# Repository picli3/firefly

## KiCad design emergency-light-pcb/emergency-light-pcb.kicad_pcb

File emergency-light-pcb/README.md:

# FIREFLY — PCB de lámpara de emergencia

> Primer borrador de documentación de la placa. Las imágenes se generan directamente desde el archivo KiCad actual.

## Vista 3D

| Vista isométrica |
|---|
|  |

| Vista superior | Vista inferior |
|---|---|
|  |  |

La vista 3D no muestra el cuerpo del módulo U1 porque el modelo STEP configurado para el footprint no está disponible en la ruta local de KiCad. Sí se muestran sus pads, serigrafía y keepout.

## 1. Descripción

Esta PCB implementa el controlador y monitor de una lámpara de emergencia conectada por Zigbee. La placa integra:

- Un módulo inalámbrico **ESP32-H2-MINI-1** como controlador principal.
- Medición de corriente, tensión y potencia mediante **INA226**.
- Entrada de temperatura mediante un divisor con NTC.
- Simulación de pérdida de alimentación de la lámpara mediante un relé.
- Regulación local de `+7.5V` a `+5V` y `+3V3`.
- Conectores de prueba, NTC, sensado de corriente, alimentación y servicio USB.

El contacto del relé conmuta la señal de control `+7.5V` de la lámpara. Esta PCB no debe interpretarse como una etapa para conmutar directamente red de `220 VAC`.

## 2. Datos principales

| Parámetro | Valor |
|---|---|
| Nombre del diseño | FIREFLY |
| Revisión indicada en el proyecto | `v1.0.0` |
| Contorno de la PCB | `37 mm × 40 mm` |
| Capas de cobre utilizadas | `F.Cu` y `B.Cu` |
| Alimentación externa | `+7.5V` y `GND` mediante J4 |
| Comunicación inalámbrica | Zigbee / IEEE 802.15.4 mediante ESP32-H2 |
| Monitor de corriente | INA226, dirección I²C `0x40` |
| Shunt de corriente | R5 = `2 mΩ` |
| Relé | Songle `SRD-05VDC-SL-C`, bobina de `5V` |

## 3. Arquitectura eléctrica

```text
                           ┌───────────────┐
J4.1  +7.5V ───────────────┤ U3            ├── +3V3 ── U1 / U2 / U5
                           │ NCP1117-3.3  │
                           └───────────────┘
                                   │
                                   └───────────────┐
                                                   ▼
                           ┌───────────────┐    +5V ── K1 bobina
J4.1  +7.5V ───────────────┤ U4            ├─────────── D1 protección flyback
                           │ TPS76950     │
                           └───────────────┘

J4.2 señal AC ── R9/R10 ── U5 ── AC_STATUS ── U1 GPIO10

J3 VIN_P ── R5 2 mΩ ── VIN_N ── J3
              │       │
              └── U2 INA226 ── I²C ── U1 GPIO4/GPIO12

J2 NTC ── NTC_IN ── U1 GPIO1 / ADC1_CH0

U1 GPIO2 / EN_R ── R4 ── Q1 ── K1 bobina
                         │
                        R14
                         │
                        GND
```

### Dominios de alimentación

- `+7.5V`: entrada de la placa, alimentación de U3/U4 y señal que se entrega al controlador de la lámpara a través del contacto del relé.
- `+5V`: salida de U4 para la bobina de K1 y el circuito de protección asociado.
- `+3V3`: salida de U3 para U1, U2, U5, pull-ups y circuitos de señal.
- `GND`: retorno común de la lógica y de las fuentes de la placa.

## 4. Pinout del ESP32-H2-MINI-1

| Pin físico U1 | Señal en PCB | Función |
|---:|---|---|
| 3 | `+3V3` | Alimentación principal del módulo |
| 5 | `/EN_R` | Control del relé desde GPIO2 |
| 8 | `/EN_MCU` | Habilitación/reset del módulo |
| 10 | `/NTC_IN` | Medición del NTC, GPIO1 / ADC1_CH0 |
| 15 | `VBAT` | Nodo de alimentación interno del módulo; en la configuración por defecto no requiere alimentación externa |
| 16 | `/SCL` | I²C SCL, GPIO12 |
| 18 | `/SDA` | I²C SDA, GPIO4 |
| 19 | `/TEST_BUTTON` | Pulsador de prueba, GPIO5 |
| 20 | `/AC_STATUS` | Estado de presencia de AC, GPIO10 |
| 21 | `/ALERT` | Alerta del INA226, GPIO11 |
| 26 | `USB_D-` | USB D− mediante R13 de 22 Ω |
| 27 | `USB_D+` | USB D+ mediante R12 de 22 Ω |
| 1, 2, 11, 14, 36–53 | `GND` | Retorno y pad expuesto del módulo |

El firmware de `h2-emergency-light` utiliza el mismo contrato: SDA=`GPIO4`, SCL=`GPIO12`, relé=`GPIO2`, NTC=`GPIO1`, botón=`GPIO5`, `AC_STATUS`=`GPIO10` y `ALERT`=`GPIO11`.

El archivo del proyecto conserva el identificador de footprint `RF_Module:ESP32-C6-MINI-1`, aunque el símbolo, el valor y la asignación de pads corresponden al ESP32-H2-MINI-1. La equivalencia mecánica de la huella debe mantenerse documentada y verificada para el componente montado.

## 5. Función de los conectores

### J1 — TEST

| Pin | Señal | Función |
|---:|---|---|
| 1 | `/TEST_BUTTON` | Entrada del pulsador de prueba hacia U1 GPIO5 |
| 2 | `GND` | Retorno común |

### J2 — NTC

| Pin | Señal | Función |
|---:|---|---|
| 1 | `/NTC_IN` | Nodo del divisor NTC hacia U1 GPIO1 / ADC1_CH0 |
| 2 | `GND` | Retorno del sensor |

### J3 — Sensado de corriente

J3 expone los dos lados del shunt R5 para insertar el circuito de corriente de la lámpara y permitir que U2 mida la caída diferencial.

| Pin | Señal | Función |
|---:|---|---|
| 1 | `VIN_P` | Lado positivo del shunt, hacia INA226 VIN+ |
| 2 | `VIN_N` | Lado negativo del shunt, hacia INA226 VIN− y VBUS |

La polaridad y el sentido de corriente deben respetarse para que el signo de la medición sea el esperado por el firmware.

### J4 — POWER / señal de lámpara

| Pin | Señal | Función |
|---:|---|---|
| 1 | `+7.5V` | Entrada de alimentación de la placa y referencia para la señal de AC |
| 2 | `Net-(J4-Pin_2)` | Señal conmutada hacia el controlador de la lámpara; también alimenta el divisor R9/R10 para generar `AC_STATUS` |
| 3 | `GND` | Retorno de alimentación |

J4.2 es una señal DC de baja tensión. No debe conectarse directamente a la red eléctrica.

### J5 — USB / servicio

J5 es un header de servicio para programación o pruebas del módulo.

| Pin | Señal | Función |
|---:|---|---|
| 1 | `+7.5V` mediante R11 de 0 Ω | Alimentación expuesta del circuito de servicio |
| 2 | `USB_D-` mediante R13 de 22 Ω | USB D− hacia U1 GPIO26 |
| 3 | `USB_D+` mediante R12 de 22 Ω | USB D+ hacia U1 GPIO27 |
| 4 | `GND` | Retorno común |

El footprint de J5 está excluido actualmente de la BOM y todavía utiliza un conector genérico. Si se montará físicamente, debe definirse su número de parte y confirmar la orientación del cableado antes de fabricar.

## 6. Bloques funcionales

### U1 — ESP32-H2-MINI-1

Controlador Zigbee de la lámpara. Gestiona el relé, el botón de prueba, la temperatura, el estado de alimentación y las mediciones del INA226.

`VBAT` corresponde al nodo de alimentación interno del módulo. Según la configuración por defecto del ESP32-H2-MINI-1, está conectado internamente a la alimentación de 3,3 V; no se debe añadir una fuente externa independiente a ese pin.

### U2 — INA226AIDGSR

Monitor de corriente y potencia por I²C. Usa dirección `0x40`, pull-ups en SDA/SCL y una resistencia shunt R5 de `2 mΩ`. La alerta se entrega a U1 mediante `/ALERT`.

### U3 — NCP1117ST33T3G

Regulador lineal de `+7.5V` a `+3V3`. C3 y C4 proporcionan el filtrado de entrada y salida.

### U4 — TPS76950DBVR

Regulador lineal de `+7.5V` a `+5V`. Su salida alimenta la bobina de K1 y el circuito de rueda libre.

### U5 — NC7SZ125M5X

Buffer lógico alimentado a `+3V3`. Convierte el nivel del divisor R9/R10 en una señal limpia de `3.3V` para `AC_STATUS`/GPIO10. OE está fijado a GND para mantenerlo habilitado.

### K1, Q1 y D1 — simulación de pérdida de AC

K1 es un relé SPDT Songle `SRD-05VDC-SL-C`. Q1, controlado por U1 GPIO2 mediante R4, conmuta la bobina; R14 mantiene la compuerta en estado apagado durante reset y D1 absorbe el pulso inductivo.

La intención funcional es que el contacto normalmente cerrado mantenga presente `+7.5V` en J4.2 cuando el relé está desenergizado. Al energizar K1, el contacto se abre y la lámpara interpreta una pérdida de alimentación.

**Nota de montaje:** confirmar la correspondencia entre la numeración física del Songle y el footprint antes de liberar Gerbers. El número de pin del símbolo genérico de KiCad no sustituye la verificación contra el dibujo del fabricante.

## 7. Componentes de soporte relevantes

| Referencia | Valor | Función |
|---|---:|---|
| C1, C6, C7 | 100 nF | Desacoplo local de U2, U1 y U5 |
| C2–C5, C8 | 10 µF | Filtrado y reserva en los reguladores y U1 |
| C9 | 1 µF | Retardo RC de `/EN_MCU` junto con R1 de 10 kΩ |
| R1–R3, R6–R8, R10 | 10 kΩ | Pull-ups y polarización de señales |
| R4 | 3.3 kΩ | Resistencia serie de compuerta de Q1 |
| R5 | 2 mΩ | Shunt de medición de corriente |
| R9 | 12.4 kΩ | Rama superior del divisor de `AC_STATUS` |
| R11 | 0 Ω | Enlace de alimentación hacia J5; selección actual del proyecto |
| R12, R13 | 22 Ω | Terminación serie de USB D+/D− |
| R14 | 100 kΩ | Pull-down de compuerta de Q1 |

## 8. Estado del borrador

La documentación corresponde al estado actual de los archivos KiCad y no sustituye una liberación de fabricación. Antes de fabricar conviene completar estas comprobaciones:

- Sincronizar el pad 15 de U1 entre esquemático y PCB después de modelar `VBAT` como conexión interna/no externa.
- Confirmar la numeración física de K1, especialmente la pareja de pines de bobina y los contactos COM/NC/NO.
- Confirmar que J5 será montado; si no se utiliza, marcarlo explícitamente como no poblado.
- Repetir ERC/DRC con paridad esquemático–PCB después de cualquier sincronización.
- Revisar las excepciones intencionales de serigrafía alrededor de U1 y el keepout de antena durante la revisión mecánica final.
- Generar Gerbers, taladros y archivos de posición únicamente después de cerrar esas comprobaciones.

## 9. Archivos del proyecto

- [Proyecto KiCad](emergency-light-pcb.kicad_pro)
- [Esquemático principal](emergency-light-pcb.kicad_sch)
- [Hoja jerárquica del INA226](INA226.kicad_sch)
- [PCB](emergency-light-pcb.kicad_pcb)
- [Reporte de revisión de activos](REPORTE_REVISION_ACTIVOS_2026-09-07.md)
- [Reporte de revisión del circuito](REPORTE_REVISION_CIRCUITO.md)

Las imágenes utilizadas en este README están en [`docs/render/`](docs/render/).

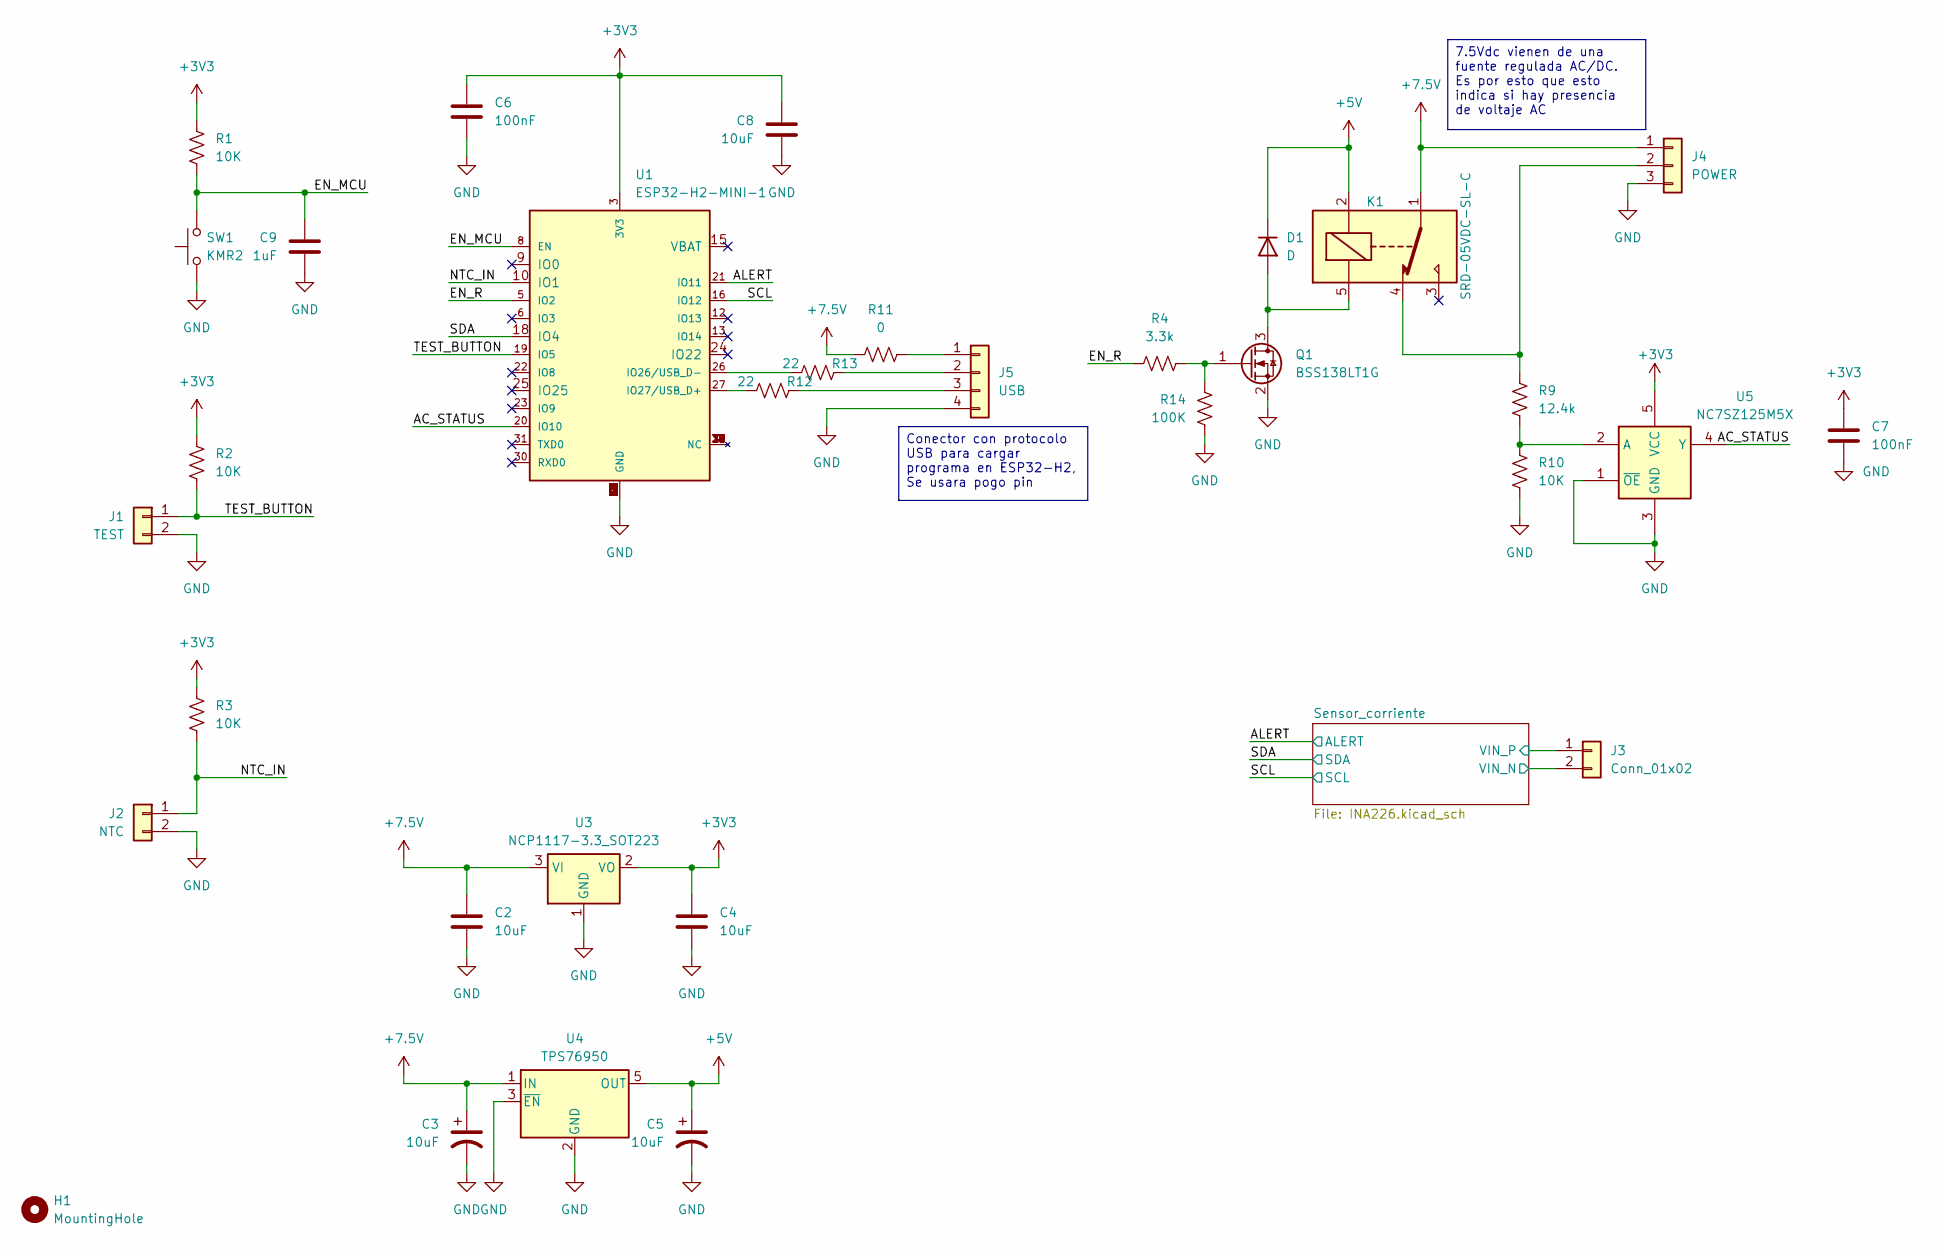
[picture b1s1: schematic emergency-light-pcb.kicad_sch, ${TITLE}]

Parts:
C2, C3, C4, C5, C8: 10uF; C_0805_2012Metric; Part # CL21A106KAYNNNE; LCSC C15850
C6, C7: 100nF; C_0603_1608Metric; Part # CC0603KRX7R9BB104; LCSC C14663
C9: 1uF; C_0603_1608Metric; Part # CC0603KRX5R8BB105; LCSC C14664
D1: D; D_SOD-123F; Part # 1N5819HW-7-F; LCSC C82544
H1: MountingHole; MountingHole_3.2mm_M3
J1: TEST; PinHeader_1x02_P2.54mm_Vertical; Part # HC-PA-2A; LCSC C2845858
J2: NTC; PinHeader_1x02_P2.00mm_Vertical; Part # HC-PA-2A; LCSC C2845858
J3: Conn_01x02; PinHeader_1x02_P2.54mm_Vertical; Part # HC-PA-2A; LCSC C2845858
J4: POWER; PinHeader_1x03_P2.54mm_Vertical; Part # B3B-PH-K-S(LF)(SN); LCSC C131339
J5: USB; PinHeader_1x04_P2.00mm_Vertical
K1: SRD-05VDC-SL-C; Relay_SPDT_SANYOU_SRD_Series_Form_C; Part # SRD-05VDC-SL-C; LCSC C35449
Q1: BSS138LT1G; SOT-23; Part # BSS138LT1G; LCSC C82045
R1, R2, R3, R10: 10K; R_0603_1608Metric; Part # RC0603FR-0710KL; LCSC C98220
R4: 3.3k; R_0603_1608Metric; Part # RC0603FR-073K3L; LCSC C108078
R9: 12.4k; R_0805_2012Metric; Part # RMC080512.4K1%N; LCSC C325850
R11: 0; R_0603_1608Metric; Part # 0603WAF0000T5E; LCSC C21189
R12, R13: 22; R_0603_1608Metric; Part # 0603WAF220JT5E; LCSC C23345
R14: 100K; R_0603_1608Metric; Part # RC0603FR-07100KL; LCSC C14675
SW1: KMR2; SW_Push_1P1T_NO_CK_KMR2; Part # KMR223GLFG; LCSC C221678
U1: ESP32-H2-MINI-1; ESP32-C6-MINI-1; Part # ESP32-H2-MINI-1-N4; LCSC C18203134
U3: NCP1117-3.3_SOT223; SOT-223-3_TabPin2; Part # NCP1117ST33T3G; LCSC C26537
U4: TPS76950; SOT-23-5; Part # TPS76950DBVR; LCSC C2842394
U5: NC7SZ125M5X; SOT-23-5; Part # NC7SZ125M5X; LCSC C7420

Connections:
+3V3: C4.1, C6.1, C7.1, C8.1, R1.2, R2.2, R3.2, U1.3 (3V3), U3.2 (VO), U5.5 (VCC); also elsewhere on the board
+5V: C5.1, D1.1 (K), K1.2, U4.5 (OUT)
+7.5V: C2.1, C3.1, J4.1, K1.1, R11.1, U3.3 (VI), U4.1 (IN)
/AC_STATUS: U1.20 (IO10), U5.4 (Y)
/ALERT: U1.21 (IO11); also elsewhere on the board
/EN_MCU: C9.1, R1.1, SW1.2, U1.8 (EN)
/EN_R: R4.1, U1.5 (IO2)
/NTC_IN: J2.1, R3.1, U1.10 (IO1)
/SCL: U1.16 (IO12); also elsewhere on the board
/SDA: U1.18 (IO4); also elsewhere on the board
/Sensor_corriente/VIN_N: J3.2; also elsewhere on the board
/Sensor_corriente/VIN_P: J3.1; also elsewhere on the board
/TEST_BUTTON: J1.1, R2.1, U1.19 (IO5)
GND: C2.2, C3.2, C4.2, C5.2, C6.2, C7.2, C8.2, C9.2, J1.2, J2.2, J4.3, J5.4, Q1.2 (S), R10.1, R14.2, SW1.1, U1.1 (GND), U1.2 (GND), U1.11 (GND), U1.14 (GND), U1.36 (GND), U1.37 (GND), U1.38 (GND), U1.39 (GND), U1.40 (GND), U1.41 (GND), U1.42 (GND), U1.43 (GND), U1.44 (GND), U1.45 (GND), U1.46 (GND), U1.47 (GND), U1.48 (GND), U1.49 (GND), U1.50 (GND), U1.51 (GND), U1.52 (GND), U1.53 (GND), U3.1 (GND), U4.2 (GND), U4.3 (~EN), U5.1 (~OE), U5.3 (GND); also elsewhere on the board
unnamed: D1.2 (A), K1.5, Q1.3 (D)
unnamed: J4.2, K1.4, R9.2
unnamed: J5.1, R11.2
unnamed: J5.2, R13.2
unnamed: J5.3, R12.2
unnamed: Q1.1 (G), R4.2, R14.1
unnamed: R13.1, U1.26 (IO26/USB_D-)
unnamed: R12.1, U1.27 (IO27/USB_D+)
unnamed: R9.1, R10.2, U5.2 (A)

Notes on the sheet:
Conector con protocolo USB para cargar programa en ESP32-H2, Se usara pogo pin
7.5Vdc vienen de una fuente regulada AC/DC. Es por esto que esto indica si hay presencia de voltaje AC

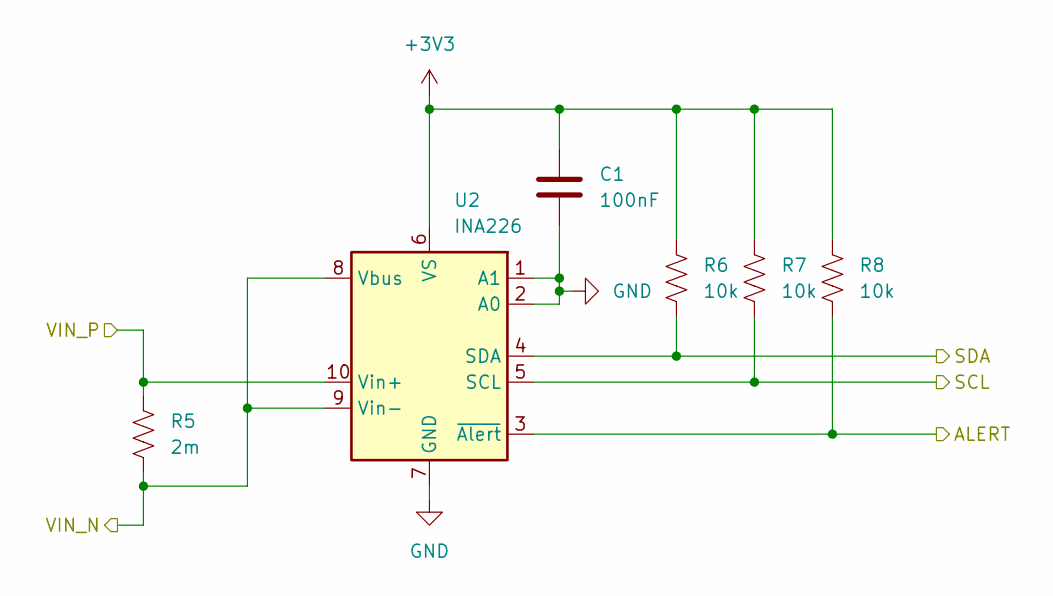
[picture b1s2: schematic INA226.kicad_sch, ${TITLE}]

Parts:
C1: 100nF; C_0603_1608Metric; Part # CC0603KRX7R9BB104; LCSC C14663
R5: 2m; R_1206_3216Metric; Part # PMR18EZPFV2L00; LCSC C92124
R6, R7, R8: 10k; R_0603_1608Metric; Part # RC0603FR-0710KL; LCSC C98220
U2: INA226; TSSOP-10_3x3mm_P0.5mm; Part # INA226AIDGSR; LCSC C49851

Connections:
+3V3: C1.1, R6.1, R7.1, R8.1, U2.6 (VS); also elsewhere on the board
/ALERT: R8.2, U2.3 (~Alert); also elsewhere on the board
/SCL: R7.2, U2.5 (SCL); also elsewhere on the board
/SDA: R6.2, U2.4 (SDA); also elsewhere on the board
/Sensor_corriente/VIN_N: R5.2, U2.8 (Vbus), U2.9 (Vin-); also elsewhere on the board
/Sensor_corriente/VIN_P: R5.1, U2.10 (Vin+); also elsewhere on the board
GND: C1.2, U2.1 (A1), U2.2 (A0), U2.7 (GND); also elsewhere on the board

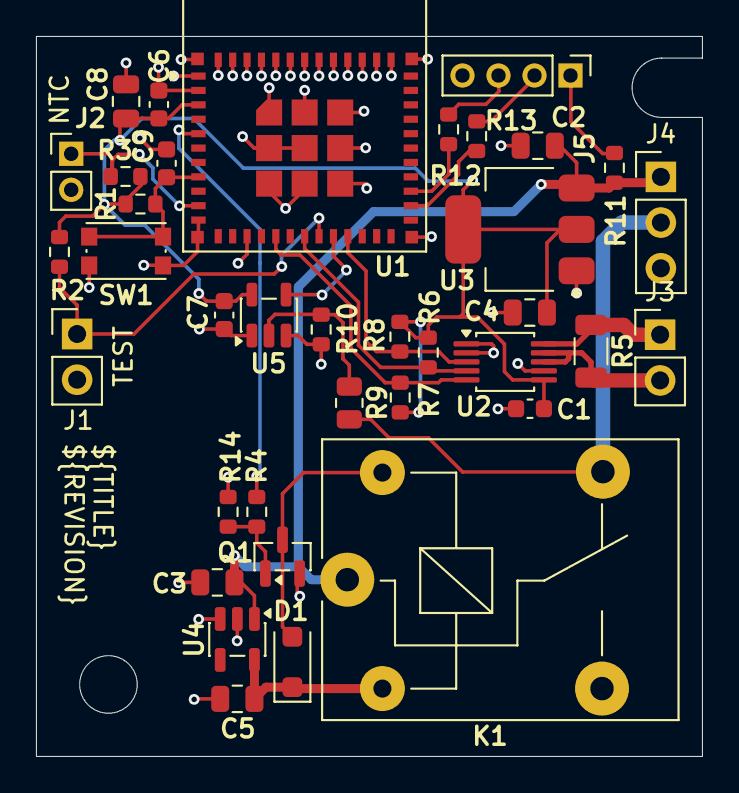
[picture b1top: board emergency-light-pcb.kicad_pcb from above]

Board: 2 copper layers, 37.0 x 40.0 mm, 38 parts (0 on the bottom side), 23 nets.

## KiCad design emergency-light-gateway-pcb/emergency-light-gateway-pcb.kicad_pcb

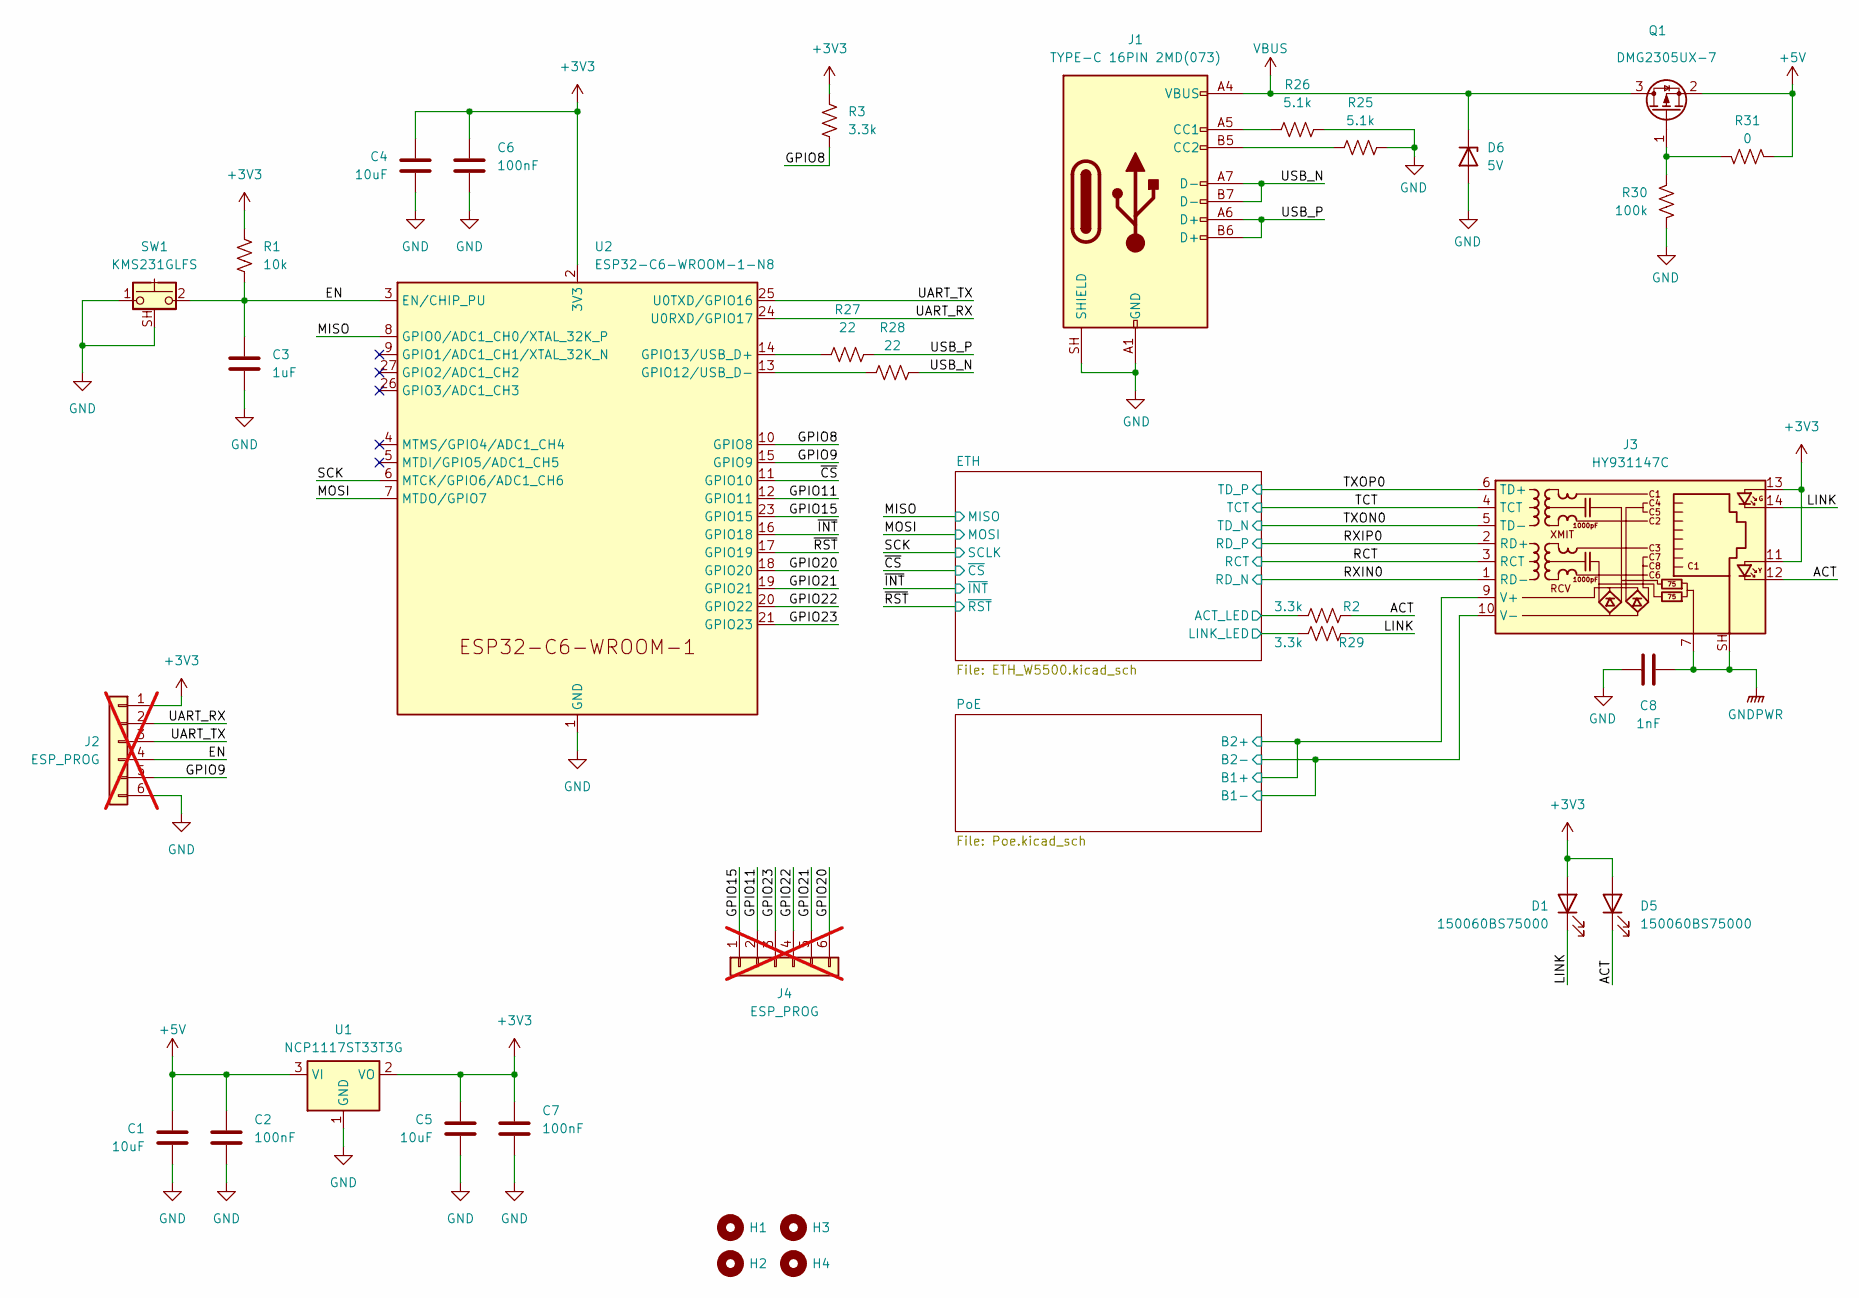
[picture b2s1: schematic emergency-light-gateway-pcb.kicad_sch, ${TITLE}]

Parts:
C1, C4, C5: 10uF; C_0805_2012Metric; MPN_1 CL21A106KAYNNNE
C2, C6, C7: 100nF; C_0603_1608Metric; MPN_1 CC0603KRX7R9BB104
C3: 1uF; C_0805_2012Metric; Rated Voltage -V; Tolerance ±10%%; MPN_1 CL21B105KBFNNNE
C8: 1nF; C_1206_3216Metric; MPN_1 1206B102K202NT
D1, D5: 150060BS75000; LED_0603_1608Metric
D6: 5V; D_SOD-123F; Forward Voltage -V; Rated Voltage -V; MPN_1 SMF5.0A
H1, H2, H3, H4: MountingHole; MountingHole_3.2mm_M3_ISO14580
J1: TYPE-C 16PIN 2MD(073); USB_C_Receptacle_GCT_USB4105-xx-A_16P_TopMnt_Horizontal; MPN_1 TYPE-C 16PIN 2MD(073)
J2: ESP_PROG; PinHeader_1x06_P2.00mm_Vertical; not fitted
J3: HY931147C; RJ45_HANRUN_HY931147C_Horizontal; MPN_1 HY931147C
J4: ESP_PROG; PinHeader_1x06_P2.54mm_Vertical; not fitted
Q1: DMG2305UX-7; SOT-23; Rated Voltage -V; MPN_1 DMG2305UX-7
R1: 10k; R_0603_1608Metric; Tolerance ±1%%; MPN_1 RC0603FR-0710KL
R2, R3, R29: 3.3k; R_0603_1608Metric; Tolerance ±1%%; MPN_1 RC0603FR-073K3L
R25, R26: 5.1k; R_0603_1608Metric; Tolerance ±1%%; MPN_1 0603WAF5101T5E
R27, R28: 22; R_0603_1608Metric; Tolerance ±1%%; MPN_1 0603WAF220JT5E
R30: 100k; R_0603_1608Metric; Tolerance ±1%%; MPN_1 RC0603FR-07100KL
R31: 0; R_0603_1608Metric; Tolerance ±1%%; MPN_1 0603WAF0000T5E
SW1: KMS231GLFS; SW_SPST_CK_KMS2xxGP; MPN_1 KMS231GLFS
U1: NCP1117ST33T3G; SOT-223-3_TabPin2; MPN_1 NCP1117ST33T3G
U2: ESP32-C6-WROOM-1-N8; ESP32-C6-WROOM-1; MPN_1 ESP32-C6-WROOM-1-N8

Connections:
+3V3: C4.1, C5.1, C6.1, C7.1, D1.2 (A), D5.2 (A), J2.1, J3.11, J3.13, R1.1, R3.1, U1.2 (VO), U2.2 (3V3); also elsewhere on the board
+5V: C1.1, C2.1, Q1.2 (S), R31.2, U1.3 (VI); also elsewhere on the board
/ACT: D5.1 (K), J3.12, R2.2
/EN: C3.1, J2.4, R1.2, SW1.2, U2.3 (EN/CHIP_PU)
/ETH/ACT_LED: R2.1; also elsewhere on the board
/ETH/LINK_LED: R29.1; also elsewhere on the board
/GPIO8: R3.2, U2.10 (GPIO8)
/GPIO9: J2.5, U2.15 (GPIO9)
/GPIO11: J4.2, U2.12 (GPIO11)
/GPIO15: J4.1, U2.23 (GPIO15)
/GPIO20: J4.6, U2.18 (GPIO20)
/GPIO21: J4.5, U2.19 (GPIO21)
/GPIO22: J4.4, U2.20 (GPIO22)
/GPIO23: J4.3, U2.21 (GPIO23)
/LINK: D1.1 (K), J3.14, R29.2
/MISO: U2.8 (GPIO0/ADC1_CH0/XTAL_32K_P); also elsewhere on the board
/MOSI: U2.7 (MTDO/GPIO7); also elsewhere on the board
/PoE/B1+: J3.9 (V+); also elsewhere on the board
/PoE/B1-: J3.10 (V-); also elsewhere on the board
/RCT: J3.3 (RCT); also elsewhere on the board
/RXIN0: J3.1 (RD-); also elsewhere on the board
/RXIP0: J3.2 (RD+); also elsewhere on the board
/SCK: U2.6 (MTCK/GPIO6/ADC1_CH6); also elsewhere on the board
/TCT: J3.4 (TCT); also elsewhere on the board
/TXON0: J3.5 (TD-); also elsewhere on the board
/TXOP0: J3.6 (TD+); also elsewhere on the board
/UART_RX: J2.2, U2.24 (U0RXD/GPIO17)
/UART_TX: J2.3, U2.25 (U0TXD/GPIO16)
/USB_N: J1.A7 (D-), J1.B7 (D-), R28.2
/USB_P: J1.A6 (D+), J1.B6 (D+), R27.2
/~CS: U2.11 (GPIO10); also elsewhere on the board
/~INT: U2.16 (GPIO18); also elsewhere on the board
/~RST: U2.17 (GPIO19); also elsewhere on the board
GND: C1.2, C2.2, C3.2, C4.2, C5.2, C6.2, C7.2, C8.1, D6.2 (A), J1.A1 (GND), J1.A12 (GND), J1.B1 (GND), J1.B12 (GND), J1.SH (SHIELD), J2.6, R25.2, R26.2, R30.1, SW1.1, SW1.SH (B), U1.1 (GND), U2.1 (GND), U2.28 (GND), U2.29 (GND); also elsewhere on the board
GNDPWR: C8.2, J3.7, J3.SH
unnamed: J1.A5 (CC1), R26.1
unnamed: J1.B5 (CC2), R25.1
unnamed: Q1.1 (G), R30.2, R31.1
unnamed: R28.1, U2.13 (GPIO12/USB_D-)
unnamed: R27.1, U2.14 (GPIO13/USB_D+)
VBUS: D6.1 (K), J1.A4 (VBUS), J1.A9 (VBUS), J1.B4 (VBUS), J1.B9 (VBUS), Q1.3 (D)

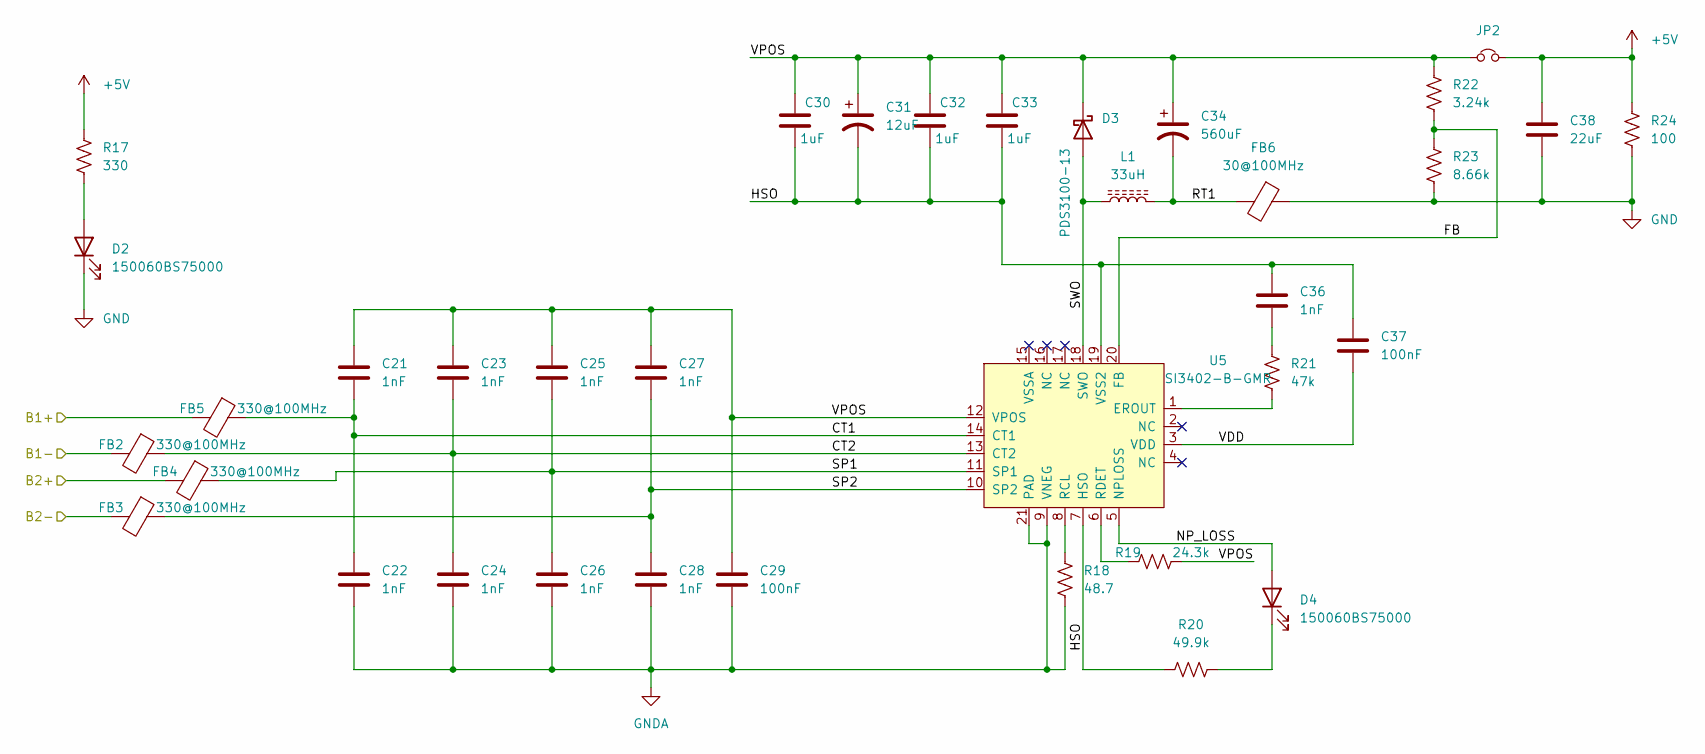
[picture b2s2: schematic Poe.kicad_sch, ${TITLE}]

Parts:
C21, C22, C23, C24, C25, C26, C27, C28: 1nF; C_0603_1608Metric; Rated Voltage -V; Tolerance ±10%%; MPN_1 CL10B102KC8NNNC
C29: 100nF; C_0805_2012Metric; Rated Voltage -V; Tolerance ±10%%; MPN_1 FTC0805X7R101-104KNE
C30, C32, C33: 1uF; C_1210_3225Metric; Rated Voltage -V; Tolerance ±10%%; Mfg Part # CL31B105KCHNNNE
C31: 12uF; CP_Radial_D5.0mm_P2.00mm; Rated Voltage -V; Tolerance ±20%%; MPN_1 LKMB1102A120MF
C34: 560uF; CP_Radial_D6.3mm_P2.50mm; Rated Voltage 6.3VV; Tolerance ±20%%; Mfg Part # T495D477M006ATE045
C36: 1nF; C_0603_1608Metric; Mfg Part # 06035C102KAT2A
C37: 100nF; C_0603_1608Metric; Mfg Part # CC0603ZRY5V9BB104
C38: 22uF; C_0805_2012Metric; Mfg Part # GRM21BR61E226ME44L
D2, D4: 150060BS75000; LED_0603_1608Metric
D3: PDS3100-13; D_PowerDI-5; Forward Voltage -V; Rated Voltage 100VV; MPN_1 PDS3100-13
FB2, FB3, FB4, FB5: 330@100MHz; L_0805_2012Metric; Tolerance ±25%%; Mfg Part # BLM21SP331SH1D
FB6: 30@100MHz; L_0805_2012Metric; Tolerance ±25%%; Mfg Part # MPZ1608S300ATAH0
JP2: Jumper_NC_Small; SolderJumper-2_P1.3mm_Bridged2Bar_RoundedPad1.0x1.5mm; Mfg Part # DNP
L1: 33uH; L_SXN_SMDRI127; Tolerance ±20%%; MPN_1 SMDRI127-330MT
R17: 330; R_0603_1608Metric; Tolerance ±1%%; Mfg Part # RC0603FR-07330RL
R18: 48.7; R_0603_1608Metric; Tolerance -%
R19: 24.3k; R_0603_1608Metric; Tolerance -%; Mfg Part # RC0603FR-0724K3L
R20: 49.9k; R_0603_1608Metric; Tolerance -%; Mfg Part # RC0603FR-0749K9L
R21: 47k; R_0603_1608Metric; Tolerance -%; Mfg Part # RC0603JR-0747KL
R22: 3.24k; R_0603_1608Metric; Tolerance -%; Mfg Part # RC0603FR-073K24L
R23: 8.66k; R_0603_1608Metric; Tolerance ±1%%; Mfg Part # RC0603FR-078K66L
R24: 100; R_1210_3225Metric; Tolerance ±1%%; Mfg Part # RC0603JR-07100RL
U5: SI3402-B-GMR; SI3402-X; Rated Voltage 37V~57VV; Mfg Part # SI3402-B-GMR; LCSC C510771

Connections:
+5V: C38.1, JP2.2, R17.1, R24.1; also elsewhere on the board
/PoE/B1+: FB4.2, FB5.2; also elsewhere on the board
/PoE/B1-: FB2.2, FB3.2; also elsewhere on the board
/PoE/CT1: C21.2, C22.1, FB5.1, U5.14 (CT1)
/PoE/CT2: C23.2, C24.1, FB2.1, U5.13 (CT2)
/PoE/FB: R22.2, R23.1, U5.20 (FB)
/PoE/HSO: C30.2, C31.2, C32.2, C33.2, C36.1, C37.1, R20.1, U5.7 (HSO), U5.19 (VSS2)
/PoE/NP_LOSS: D4.2 (A), U5.5 (NPLOSS)
/PoE/RT1: C34.2, FB6.2, L1.2
/PoE/SP1: C25.2, C26.1, FB4.1, U5.11 (SP1)
/PoE/SP2: C27.2, C28.1, FB3.1, U5.10 (SP2)
/PoE/SWO: D3.2 (A), L1.1, U5.18 (SWO)
/PoE/VDD: C37.2, U5.3 (VDD)
/PoE/VPOS: C21.1, C23.1, C25.1, C27.1, C29.1, C30.1, C31.1, C32.1, C33.1, C34.1, D3.1 (K), JP2.1, R19.1, R22.1, U5.12 (VPOS)
GND: C38.2, D2.1 (K), FB6.1, R23.2, R24.2; also elsewhere on the board
GNDA: C22.2, C24.2, C26.2, C28.2, C29.2, R18.2, U5.9 (VNEG), U5.21 (PAD)
unnamed: C36.2, R21.1
unnamed: D2.2 (A), R17.2
unnamed: D4.1 (K), R20.2
unnamed: R21.2, U5.1 (EROUT)
unnamed: R18.1, U5.8 (RCL)
unnamed: R19.2, U5.6 (RDET)

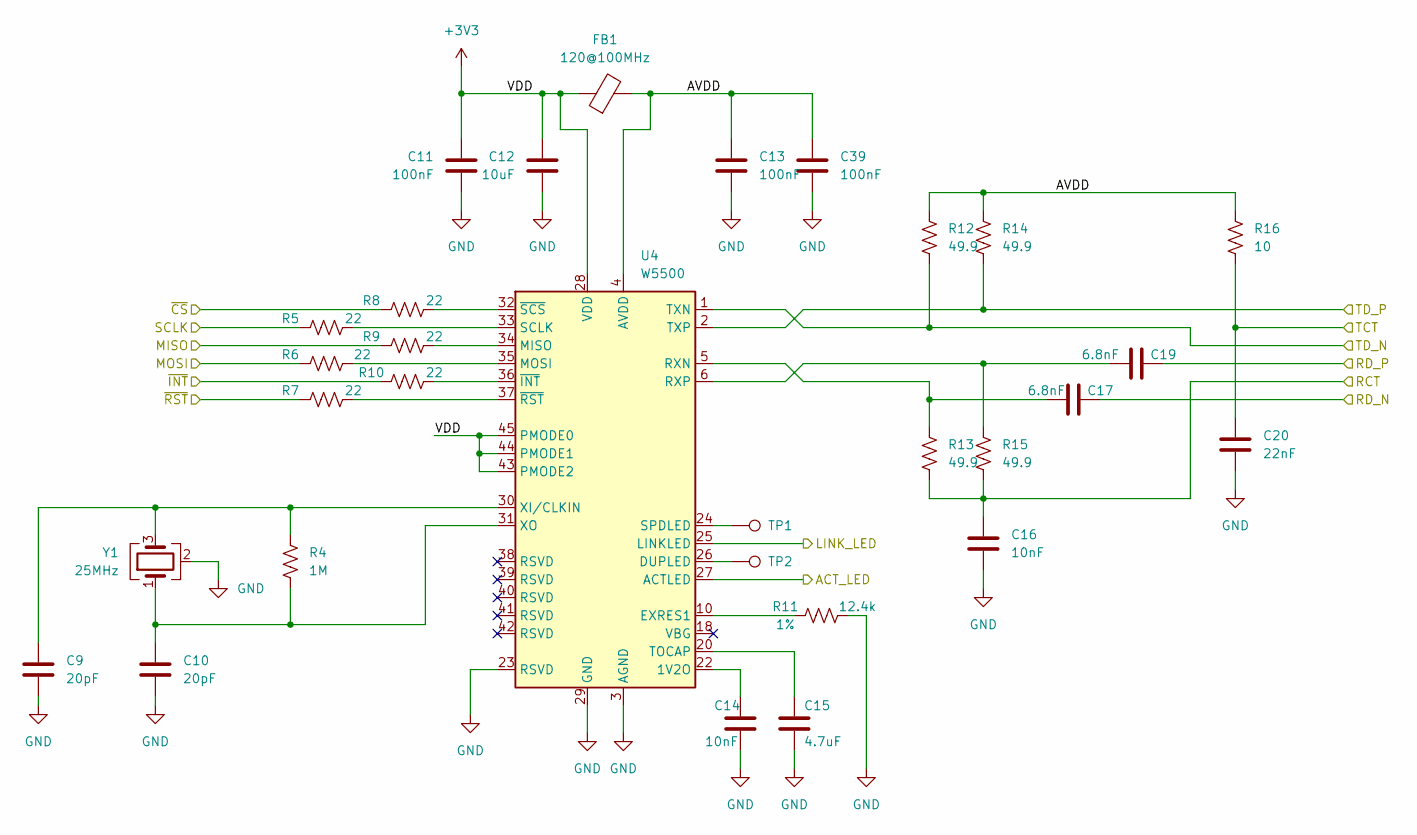
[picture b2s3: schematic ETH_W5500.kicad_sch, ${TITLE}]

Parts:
C9, C10: 20pF; C_0603_1608Metric; Rated Voltage -V; Tolerance ±5%%; MPN_1 CC0603JRNPO9BN200
C11, C13, C39: 100nF; C_0603_1608Metric; Part # CL10B104KO8NNNC; LCSC C66501
C12: 10uF; C_0805_2012Metric; Part # CL21A106KPFNNNE; LCSC C15850
C14, C16: 10nF; C_0603_1608Metric; Part # CC0603KRX7R7BB103; LCSC C519406
C15: 4.7uF; C_0603_1608Metric; MPN_1 CL10A475KP8NNNC
C17, C19: 6.8nF; C_0603_1608Metric; Rated Voltage -V; Tolerance ±10%%; Part # CC0603KRX7R9BB682; LCSC C107097
C20: 22nF; C_0603_1608Metric; Rated Voltage -V; Tolerance ±10%%; Part # CC0603KRX7R9BB223; LCSC C106222
FB1: 120@100MHz; L_0603_1608Metric; Tolerance ±25%%; Part # CBM160808U121T; LCSC C62708
R4: 1M; R_0603_1608Metric; Tolerance ±1%%; MPN_1 RC0603FR-071ML
R5, R6, R7, R8, R9, R10: 22; R_0603_1608Metric; Tolerance ±1%%; MPN_1 0603WAF220JT5E
R11: 12.4k; R_0805_2012Metric; Tolerance ±1%%; Part # RMC080512.4K1%N; LCSC C325850
R12, R13, R14, R15: 49.9; R_0603_1608Metric; Tolerance ±1%%; Part # WR06X49R9FTL; LCSC C163926
R16: 10; R_0603_1608Metric; Tolerance ±1%%; Part # 0603WAF100JT5E; LCSC C22859
TP1, TP2: TestPoint; TestPoint_Pad_1.0x1.0mm
U4: W5500; LQFP-48_7x7mm_P0.5mm; Rated Voltage 3.3VV; MPN_1 W5500
Y1: 25MHz; Crystal_SMD_SeikoEpson_FA238V-4Pin_3.2x2.5mm; Frequency Tolerance -ppm; Rated Voltage -V; MPN_1 XTM32025000JT00351001

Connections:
+3V3: C11.1, C12.1, FB1.1, U4.28 (VDD), U4.43 (PMODE2), U4.44 (PMODE1), U4.45 (PMODE0); also elsewhere on the board
/ETH/ACT_LED: U4.27 (ACTLED); also elsewhere on the board
/ETH/AVDD: C13.1, C39.1, FB1.2, R12.2, R14.2, R16.2, U4.4 (AVDD), U4.8 (AVDD), U4.11 (AVDD), U4.15 (AVDD), U4.17 (AVDD), U4.21 (AVDD)
/ETH/LINK_LED: U4.25 (LINKLED); also elsewhere on the board
/MISO: R9.1; also elsewhere on the board
/MOSI: R6.1; also elsewhere on the board
/RCT: C16.1, R13.1, R15.1; also elsewhere on the board
/RXIN0: C17.2; also elsewhere on the board
/RXIP0: C19.2; also elsewhere on the board
/SCK: R5.1; also elsewhere on the board
/TCT: C20.1, R16.1; also elsewhere on the board
/TXON0: R12.1, U4.1 (TXN); also elsewhere on the board
/TXOP0: R14.1, U4.2 (TXP); also elsewhere on the board
/~CS: R8.1; also elsewhere on the board
/~INT: R10.1; also elsewhere on the board
/~RST: R7.1; also elsewhere on the board
GND: C9.2, C10.2, C11.2, C12.2, C13.2, C14.2, C15.2, C16.2, C20.2, C39.2, R11.2, U4.3 (AGND), U4.9 (AGND), U4.14 (AGND), U4.16 (AGND), U4.19 (AGND), U4.23 (RSVD), U4.29 (GND), U4.48 (AGND), Y1.2 (G), Y1.4 (G); also elsewhere on the board
unnamed: C14.1, U4.22 (1V2O)
unnamed: TP2.1 (1_1), U4.26 (DUPLED)
unnamed: R11.1, U4.10 (EXRES1)
unnamed: R9.2, U4.34 (MISO)
unnamed: R6.2, U4.35 (MOSI)
unnamed: C17.1, R13.2, U4.5 (RXN)
unnamed: C19.1, R15.2, U4.6 (RXP)
unnamed: R5.2, U4.33 (SCLK)
unnamed: TP1.1 (1_1), U4.24 (SPDLED)
unnamed: C15.1, U4.20 (TOCAP)
unnamed: C9.1, R4.2, U4.30 (XI/CLKIN), Y1.3
unnamed: C10.1, R4.1, U4.31 (XO), Y1.1
unnamed: R10.2, U4.36 (~INT)
unnamed: R7.2, U4.37 (~RST)
unnamed: R8.2, U4.32 (~SCS)

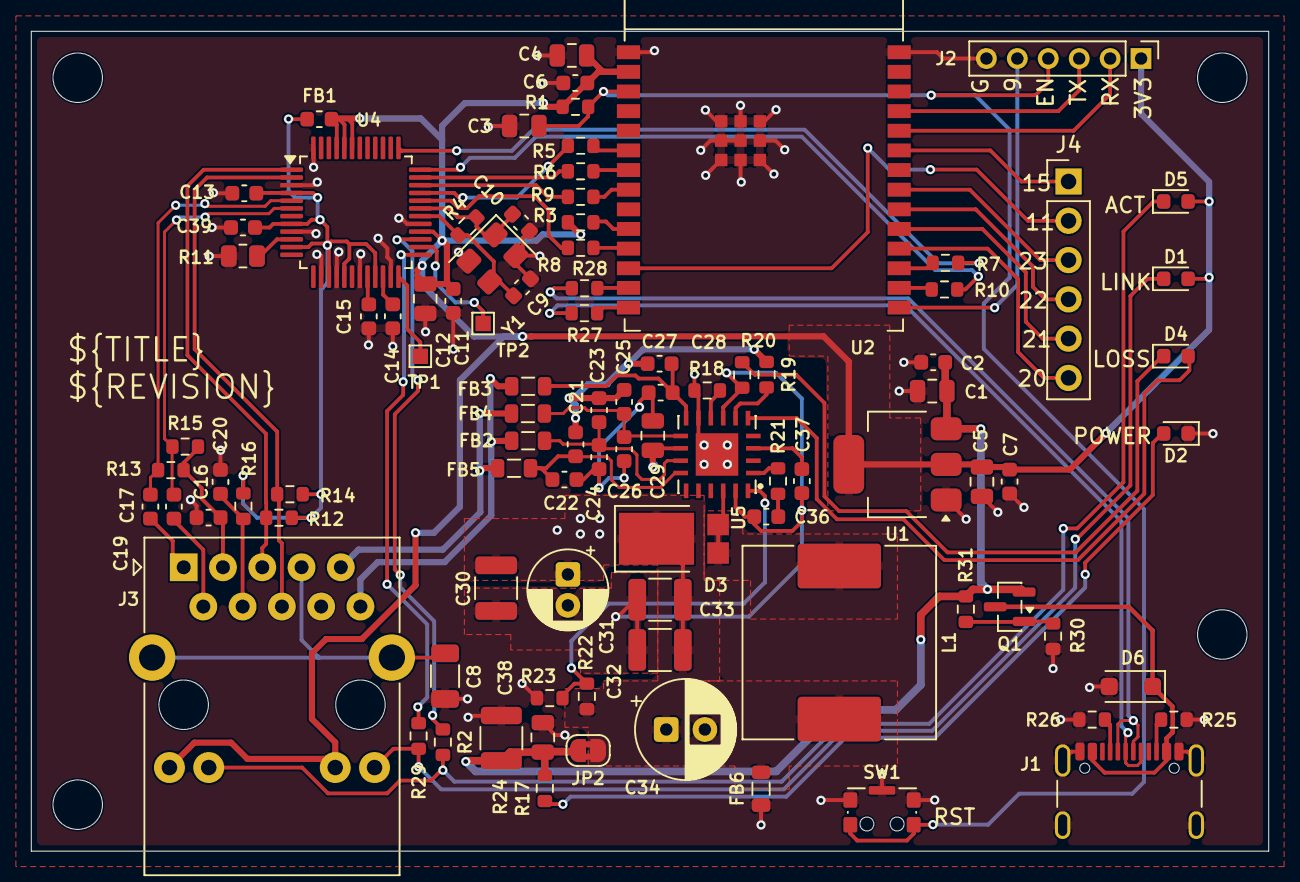
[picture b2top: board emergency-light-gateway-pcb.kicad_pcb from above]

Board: 2 copper layers, 80.0 x 53.0 mm, 99 parts (0 on the bottom side), 75 nets.
